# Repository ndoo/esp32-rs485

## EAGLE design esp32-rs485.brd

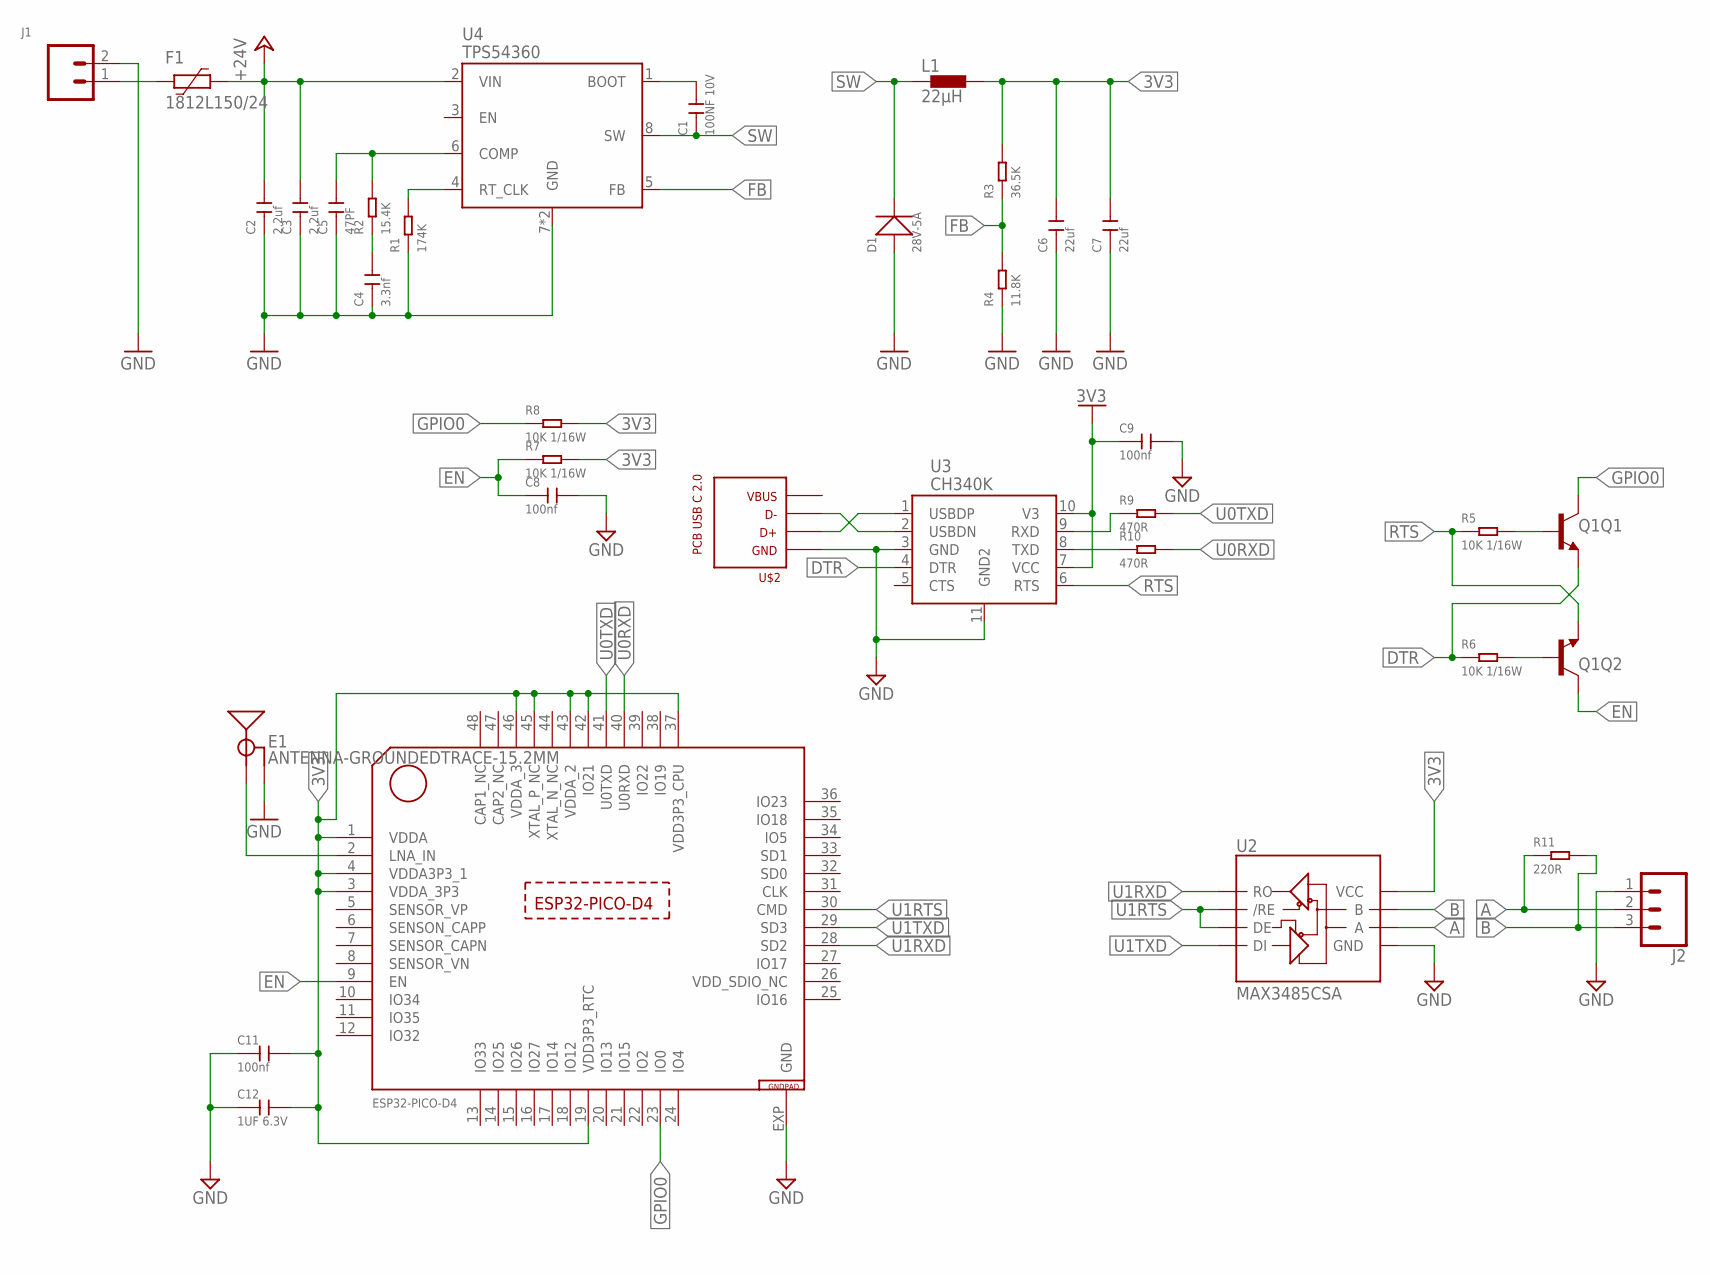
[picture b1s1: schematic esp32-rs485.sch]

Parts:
C1: 100NF 10V; C0402
C2, C3: 2.2uf; C0805; MPN CC0805KKX7R9BB225
C4: 3.3nf; C0402; MPN CC0402KRX7R9BB332
C5: 47PF; C0402
C6, C7: 22uf; C0805
C8, C9, C11: 100nf; C0402
C12: 1UF 6.3V; C0402
D1: 28V-5A; DO-214AA
E1: ANTENNA-GROUNDEDTRACE-15.2MM; TRACE_ANTENNA_2.4GHZ_15.2MM
F1: 1812L150/24; 1812L
J1: GREEN-2P-3.5; SCREWTERMINAL-3.5MM-2
J2: CONN_03SCREW; SCREWTERMINAL-3.5MM-3
L1: 22μH; XTAL660X660X300N
Q1: TRANS_NPN_DUAL-MBT3904DW1T1; SC70-6
R1: 174K; R0402; MPN RC0402FR-07174KL
R2: 15.4K; R0402; MPN RC0402FR-0715K4L
R3: 36.5K; R0402; MPN RC0402FR-0736K5L
R4: 11.8K; R0402; MPN RC0402FR-0711K8L
R5, R6, R7, R8: 10K 1/16W; R0402
R9, R10: 470R; R0402
R11: 220R; R0402; MPN RC0402FR-07220RL
U1: ESP32-PICO-D4; QFN48
U2: MAX3485CSA; SO08
U3: CH340K; SOP100P600X180-11T230X320N
U4: TPS54360; SO08-PAD
U$2: PCB_USB_C_2.0DS_2; USB_TYPE_C_DS_2

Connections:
3V3: C6.2, C7.2, C9.1, C11.2, C12.2, L1.2, R3.2, R7.2, R8.2, U1.1 (VDDA), U1.3 (VDDA_3P3), U1.4 (VDDA3P3_1), U1.19 (VDD3P3_RTC), U1.37 (VDD3P3_CPU), U1.42 (IO21), U1.43 (VDDA_2), U1.45 (XTAL_P_NC), U1.46 (VDDA_3), U2.8 (VCC), U3.7 (VCC), U3.10 (V3)
+24V: C2.2, C3.2, F1.1, U4.2 (VIN)
A: J2.2, R11.1, U2.6 (A)
B: J2.3, R11.2, U2.7 (B)
DTR: Q1.4 (E), R6.1, U3.4 (DTR)
EN: C8.1, Q1.6 (C), R7.1, U1.9 (EN)
FB: R3.1, R4.2, U4.5 (FB)
GND: C2.1, C3.1, C4.1, C5.1, C6.1, C7.1, C8.2, C9.2, C11.1, C12.1, D1.+, E1.GND, J1.2, J2.1, R1.1, R4.1, U1.EXP (GND), U2.5 (GND), U3.3 (GND), U3.11 (GND2), U4.7 (GND), U4.TP (GND), U$2.A4 (VBUS), U$2.A9 (VBUS), U$2.B4 (VBUS), U$2.B9 (VBUS)
GPIO0: Q1.3 (C), R8.1, U1.23 (IO0)
unnamed: E1.ANT (SIGNAL), U1.2 (LNA_IN)
unnamed: C1.2, U4.1 (BOOT)
unnamed: Q1.5 (B), R5.2
unnamed: F1.2, J1.1
unnamed: R1.2, U4.4 (RT_CLK)
unnamed: C4.2, R2.1
unnamed: Q1.2 (B), R6.2
unnamed: R10.1, U3.8 (TXD)
unnamed: R9.1, U3.9 (RXD)
unnamed: U3.2 (USBDN), U$2.A6 (D+), U$2.B6 (D+)
unnamed: U3.1 (USBDP), U$2.A7 (D-), U$2.B7 (D-)
unnamed: C5.2, R2.2, U4.6 (COMP)
RTS: Q1.1 (E), R5.1, U3.6 (RTS)
SW: C1.1, D1.-, L1.1, U4.8 (SW)
U0RXD: R10.2, U1.40 (U0RXD)
U0TXD: R9.2, U1.41 (U0TXD)
U1RTS: U1.30 (CMD), U2.2 (/RE), U2.3 (DE)
U1RXD: U1.28 (SD2), U2.1 (RO)
U1TXD: U1.29 (SD3), U2.4 (DI)
VDD_SDIO_NC: U1.26 (VDD_SDIO_NC)

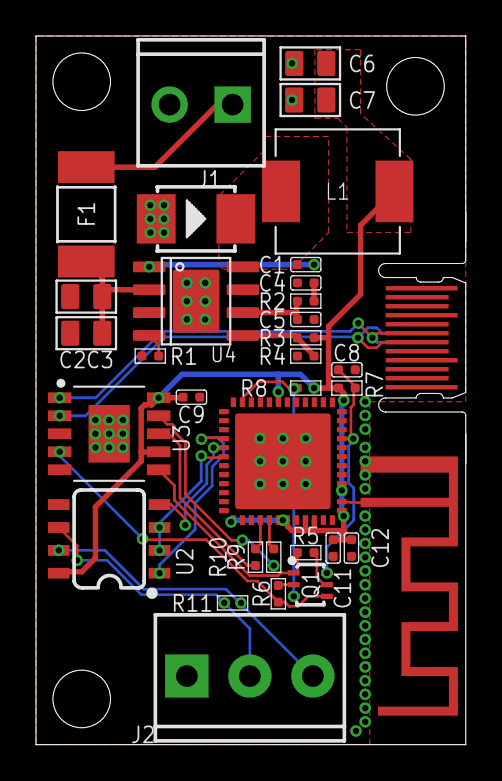
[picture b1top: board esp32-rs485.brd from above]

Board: 2 copper layers, 23.9 x 39.4 mm, 34 parts (0 on the bottom side), 28 nets.

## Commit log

2021-02-13 Change README file extension to .md
2021-02-13 Add MAX3485, CH340K and associated passives
    Add MAX3485 TTL serial to RS-485 transceiver and associated passives.
    Add CH340K USB to TTL serial chip and associated passives, ESP reset circuitry and PCB edge USB-C connector (must use 0.8mm PCB).
    Complete PCB layout.

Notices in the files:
parts and their libraries:
SparkFun-RF: Licensing: Creative Commons ShareAlike 4.0 International - https://creativecommons.org/licenses/by-sa/4.0
